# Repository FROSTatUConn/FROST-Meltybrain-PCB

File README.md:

# FROST-Meltybrain-PCB
Repository for all of the PCB design files in KiCAD for the FROST meltybrain

## COMPONENTS
- H3LIS331DL Sparkfun breakout board
- Arduino Nano microcontroller
- WS2812B RGB LEDs

## Version 2.0
**TODO:**
- **ACCELEROMETER PINS ARE FLIPPED HORIZONTALLY**
- Accelerometer insufficient spacing (too tight, increase spacing)
- Arduino pin staggering still too loose, shift pins over slightly

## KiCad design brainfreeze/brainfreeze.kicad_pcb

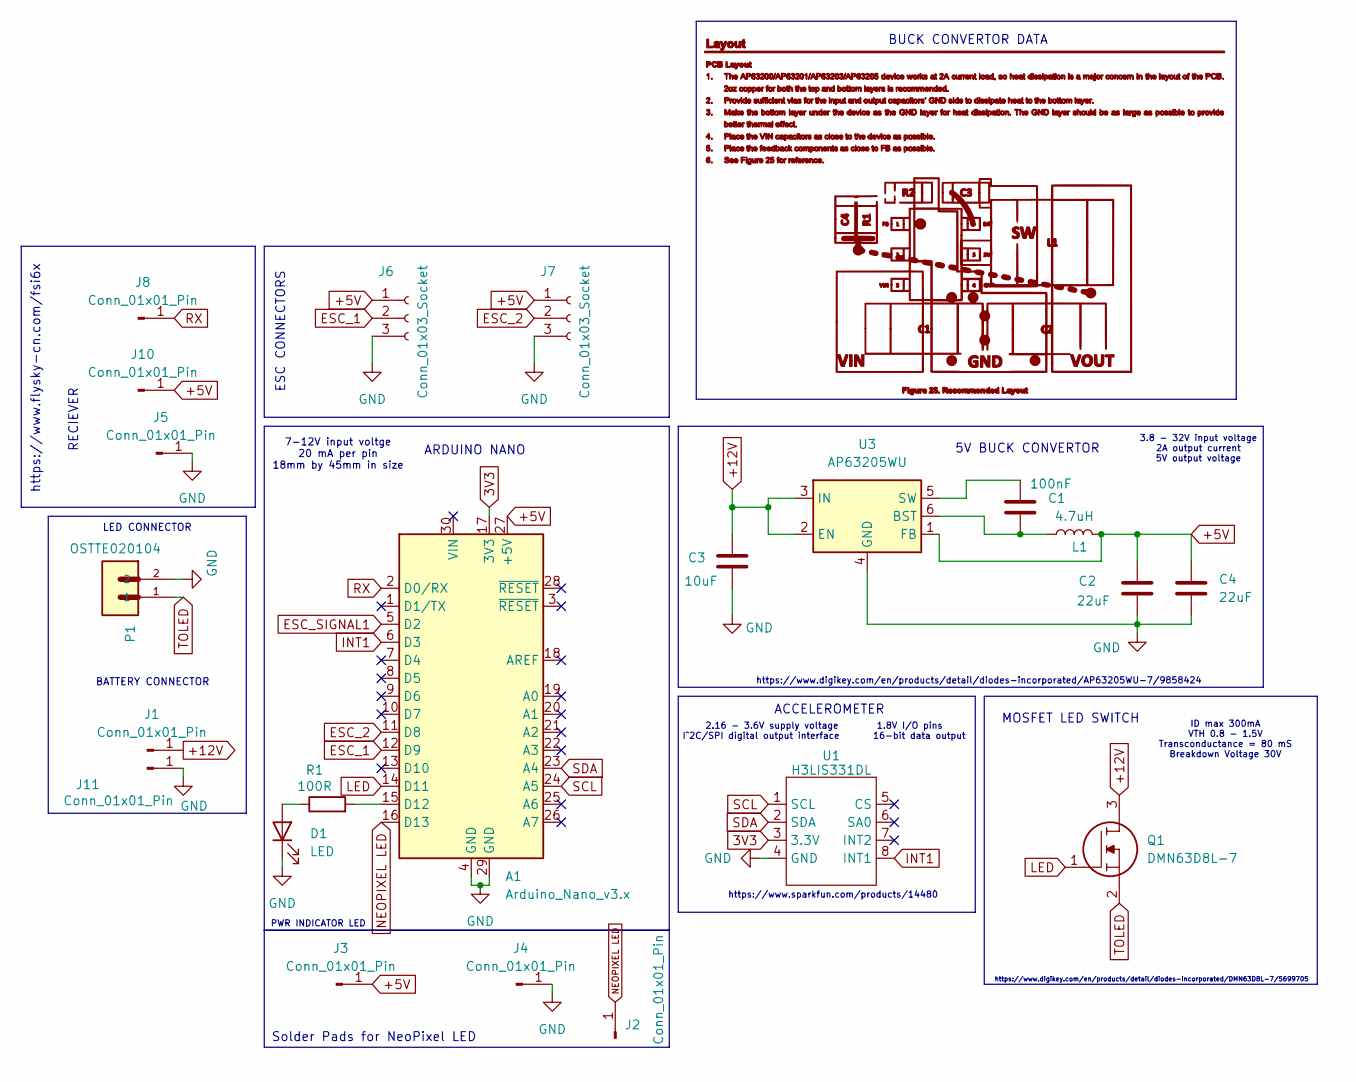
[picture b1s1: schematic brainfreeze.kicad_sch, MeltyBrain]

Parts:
A1: Arduino_Nano_v3.x; NANO_FIT
C1: 100nF; C_0402_1005Metric
C2, C4: 22uF; C_1206_3216Metric
C3: 10uF; C_0805_2012Metric
D1: LED; LED_0603_1608Metric
J1, J3, J4, J5, J10, J11: Conn_01x01_Pin; SolderWire-1sqmm_1x01_D1.4mm_OD2.7mm
J2, J8: Conn_01x01_Pin; SolderWire-0.5sqmm_1x01_D0.9mm_OD2.1mm
J6, J7: Conn_01x03_Socket; ESC CON
L1: 4.7uH; L_1210_3225Metric
P1: OSTTE020104; OST_OSTTE020104
Q1: DMN63D8L-7; MOSFET; Mouser Part Number 621-DMN63D8L-7
R1: 100R; R_0603_1608Metric
U1: H3LIS331DL; Accelerometer
U3: AP63205WU; TSOT-23-6

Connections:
3V3: A1.17 (3V3), U1.3 (3.3V)
+5V: A1.27 (+5V), C2.1, C4.1, J3.1, J6.1, J7.1, J10.1, L1.2, U3.1 (FB)
+12V: C3.1, J1.1, Q1.3, U3.2 (EN), U3.3 (IN)
ESC_1: A1.12 (D9), J6.2
ESC_2: A1.11 (D8), J7.2
ESC_SIGNAL1: A1.5 (D2)
ESC_SIGNAL2: A1.21 (A2)
ESC_SIGNAL3: A1.22 (A3)
GND: A1.4 (GND), A1.29 (GND), C2.2, C3.2, C4.2, D1.1 (K), J4.1, J5.1, J6.3, J7.3, J11.1, P1.2, U1.4 (GND), U3.4 (GND)
INT1: A1.6 (D3), U1.8 (INT1)
LED: A1.14 (D11), Q1.1
NEOPIXEL LED: A1.16 (D13), J2.1
unnamed: A1.15 (D12), R1.2
unnamed: D1.2 (A), R1.1
unnamed: C1.1, L1.1, U3.6 (BST)
unnamed: C1.2, U3.5 (SW)
RX: A1.2 (D0/RX), J8.1
SCL: A1.24 (A5), U1.1 (SCL)
SDA: A1.23 (A4), U1.2 (SDA)
TOLED: P1.1, Q1.2

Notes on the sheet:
LED CONNECTOR
ESC CONNECTORS
BUCK CONVERTOR DATA
ACCELEROMETER
RECIEVER
ID max 300mA VTH 0.8 - 1.5V Transconductance = 80 mS Breakdown Voltage 30V
MOSFET LED SWITCH
https://www.digikey.com/en/products/detail/diodes-incorporated/AP63205WU-7/9858424
https://www.flysky-cn.com/fsi6x
3.8 - 32V input voltage 2A output current 5V output voltage
Solder Pads for NeoPixel LED
PWR INDICATOR LED
7-12V input voltge 20 mA per pin 18mm by 45mm in size
https://www.sparkfun.com/products/14480
BATTERY CONNECTOR
5V BUCK CONVERTOR
ARDUINO NANO
https://www.digikey.com/en/products/detail/diodes-incorporated/DMN63D8L-7/5699705
2.16 - 3.6V supply voltage 1.8V I/O pins I^2C/SPI digital output interface 16-bit data output

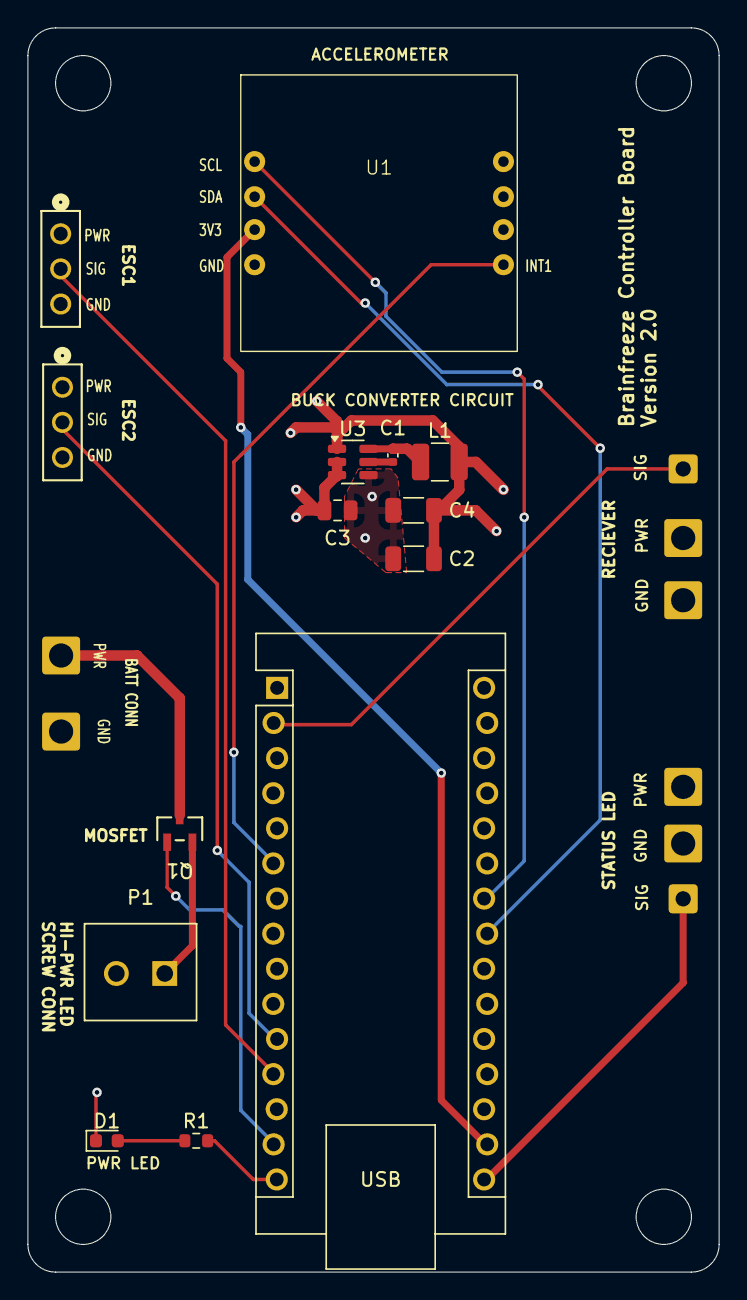
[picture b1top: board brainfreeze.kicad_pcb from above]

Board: 4 copper layers, 50.0 x 90.0 mm, 22 parts (0 on the bottom side), 17 nets.

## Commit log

2025-02-17 Add files via upload
    Schematic, PCB, and footprints for MeltyBrain robot
2025-02-18 updated with screwholes
2025-03-31 Add files via upload
    Final PCB design
2025-03-31 Final PCB Design
2025-04-08 Updated PCB
2025-04-15 Gerber files
2025-04-15 Created gerber files
2025-04-15 added .gitignore for *.zip, fillet + dimensioned PCB
2025-04-15 Added version number to board
2025-04-28 updated README.md with todo
